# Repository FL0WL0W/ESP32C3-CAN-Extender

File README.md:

# ESP32C3 CAN Extender

This module uses an ESP32C3 with WiFi and BLE. 
It has 3 configurable outputs (5V push pull, Open Drain, 12V pullup), 4 analog or digital inputs, CAN transceiver, 
and an automotive power supply so it can be installed directly into a vehicle. It can be programmed and debugged using the edge connector that connects to any standard 
USBC cable. If you decide to order a PCB yourself, make sure to order it as 0.6mm thickness so that the PCB will fit in the USBC connector.
<br/><br/>
The purpose of this module will be to add cruise control, AC control, tachometer output, speedometer output, and fuel consumption output to my LS3 swapped BMW E30.
The LS3 is currently controlled by the stock GM E38 PCM. This PCM (Powertrain Control Module) uses the CAN bus for the aforementioned items, and this is meant to be a bridge from CAN, to 
discrete signals. This job is originally handled by the BCM (Body Control Module), However the BCM includes alot of items that are not needed for a typical swap, and there 
is not very good documentation on the various BCMs available in cars (compatibility, pinout, etc.). In the future, this car will run on an 
<a href="https://github.com/FL0WL0W/EFIGenie">EFIGenie</a> PCM once the software is more mature. This module will then be useful as a CAN extension module.
<br/><br/>
A demo program will be added soon that has all of the aforementioned features hardcoded, but the eventual goal is to utilize the work from my other repositories 
to create a configurable module that can be programmed through a web UI for various tasks. Another potential feature would be to implement an emulation of the ubiquitous ELM327 bluetooth module that can be used to connect to a phone or tablet to read diagnostic codes, read sensors, or create a digital dash.
<br/><br/>
A 3d model of the enclosure will be uploaded soon as well. The plan is to epoxy pot the pcb inside the enclosure to make it waterproof.

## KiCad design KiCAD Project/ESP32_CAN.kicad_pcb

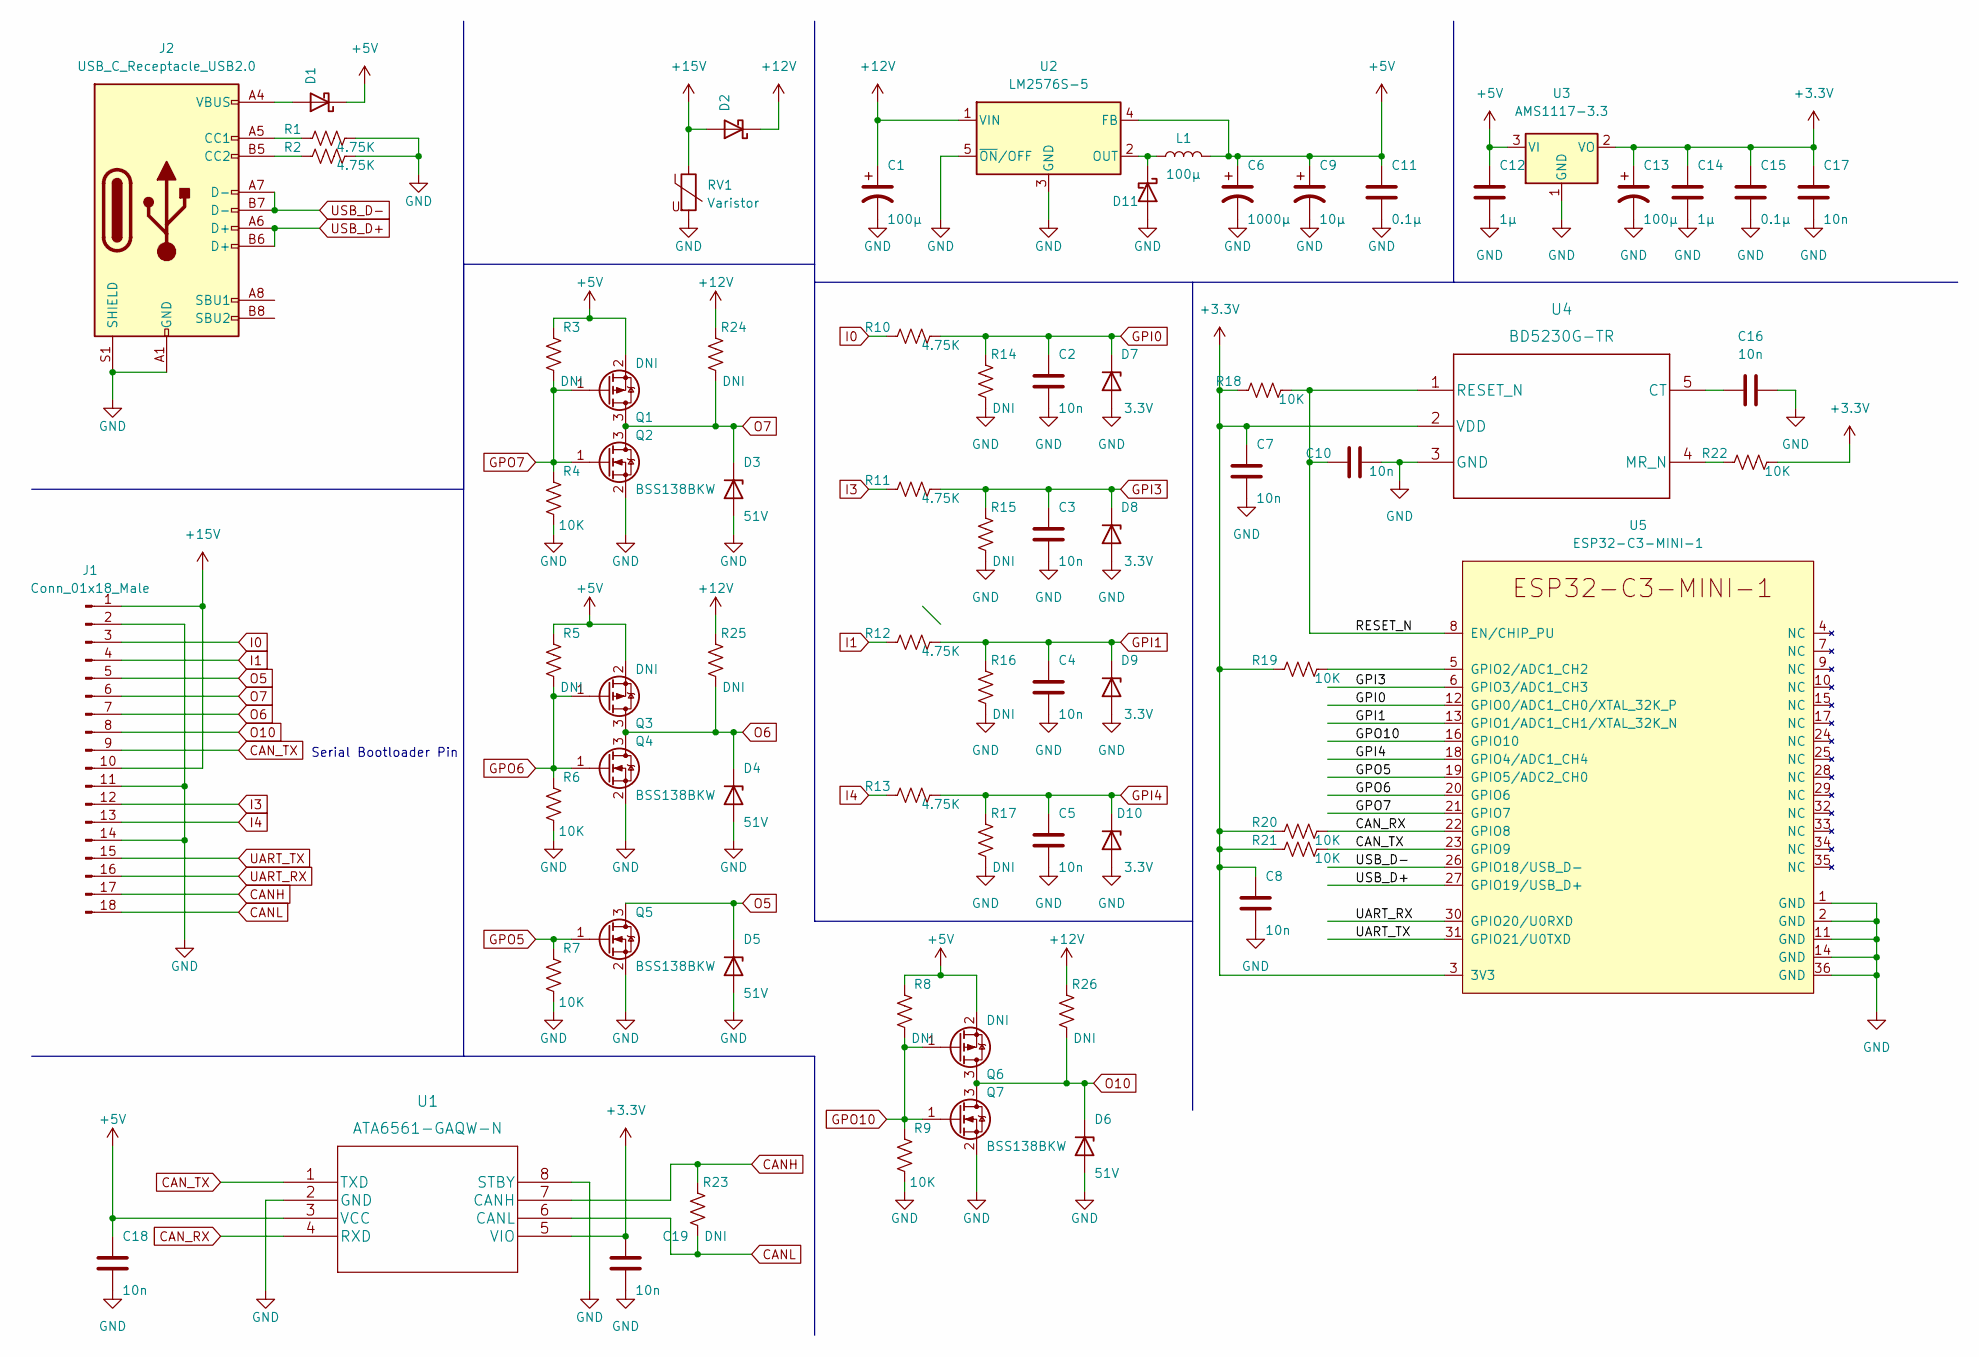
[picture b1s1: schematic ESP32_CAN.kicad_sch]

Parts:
C1, C13: 100μ; CP_Elec_10x10.5
C2, C3, C4, C5, C7, C8, C10, C16, C17, C18, C19: 10n; C_0603_1608Metric_Pad1.08x0.95mm_HandSolder
C6: 1000μ; CP_Elec_10x10.5
C9: 10μ; C_0603_1608Metric_Pad1.08x0.95mm_HandSolder
C11, C15: 0.1μ; C_0603_1608Metric_Pad1.08x0.95mm_HandSolder
C12, C14: 1μ; C_0603_1608Metric_Pad1.08x0.95mm_HandSolder
D1, D2, D11: D_Schottky; D_SOD-123
D3, D4, D5, D6: 51V; D_SOD-123
D7, D8, D9, D10: 3.3V; D_SOD-123
J1: Conn_01x18_Male; MX23A18NF1
J2: USB_C_Receptacle_USB2.0; USB_TYPE_C_DS_5
L1: 100μ; L_12x12mm_H4.5mm
Q1, Q3, Q6: DNI; SOT-323_SC-70_Handsoldering
Q2, Q4, Q5, Q7: BSS138BKW; SOT-323_SC-70_Handsoldering
R1, R2, R10, R11, R12, R13: 4.75K; R_0603_1608Metric_Pad0.98x0.95mm_HandSolder
R3, R5, R8, R14, R15, R16, R17, R23, R24, R25, R26: DNI; R_0603_1608Metric_Pad0.98x0.95mm_HandSolder
R4, R6, R7, R9, R18, R19, R20, R21, R22: 10K; R_0603_1608Metric_Pad0.98x0.95mm_HandSolder
RV1: Varistor; RV_Disc_D15.5mm_W3.9mm_P7.5mm
U1: ATA6561-GAQW-N
U2: LM2576S-5; TO-263-5_TabPin3
U3: AMS1117-3.3; SOT-223-3_TabPin2
U4: BD5230G-TR; TPS3840DL18DBVR
U5: ESP32-C3-MINI-1

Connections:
+3V3: C7.1, C8.1, C13.1, C14.1, C15.1, C17.1, C19.1, R18.1, R19.1, R20.1, R21.1, R22.2, U1.5 (VIO), U3.2 (VO), U4.2 (VDD), U5.3 (3V3)
+5V: C6.1, C9.1, C11.1, C12.1, C18.1, D1.1 (K), L1.2, Q1.2 (S), Q3.2 (S), Q6.2 (S), R3.2, R5.2, R8.2, U1.3 (VCC), U2.4 (FB), U3.3 (VI)
+12V: C1.1, D2.1 (K), R24.2, R25.2, R26.2, U2.1 (VIN)
+15V: D2.2 (A), J1.1, J1.10, RV1.1
/RESET_N: C10.1, R18.2, U4.1 (RESET_N), U5.8 (EN/CHIP_PU)
CANH: J1.17, R23.2, U1.7 (CANH)
CANL: J1.18, R23.1, U1.6 (CANL)
CAN_RX: R20.2, U1.4 (RXD), U5.22 (GPIO8)
CAN_TX: J1.9, R21.2, U1.1 (TXD), U5.23 (GPIO9)
GND: C1.2, C2.2, C3.2, C4.2, C5.2, C6.2, C7.2, C8.2, C9.2, C10.2, C11.2, C12.2, C13.2, C14.2, C15.2, C16.2, C17.2, C18.2, C19.2, D3.2 (A), D4.2 (A), D5.2 (A), D6.2 (A), D7.2 (A), D8.2 (A), D9.2 (A), D10.2 (A), D11.2 (A), J1.2, J1.11, J1.14, J2.A1 (GND), J2.A12 (GND), J2.B1 (GND), J2.B12 (GND), J2.S1 (SHIELD), Q2.2 (S), Q4.2 (S), Q5.2 (S), Q7.2 (S), R1.2, R2.2, R4.1, R6.1, R7.1, R9.1, R14.1, R15.1, R16.1, R17.1, RV1.2, U1.2 (GND), U1.8 (STBY), U2.3 (GND), U2.5 (~ON/OFF), U3.1 (GND), U4.3 (GND), U5.1 (GND), U5.2 (GND), U5.11 (GND), U5.14 (GND), U5.36 (GND)
GPI0: C2.1, D7.1 (K), R10.2, R14.2, U5.12 (GPIO0/ADC1_CH0/XTAL_32K_P)
GPI1: C4.1, D9.1 (K), R12.2, R16.2, U5.13 (GPIO1/ADC1_CH1/XTAL_32K_N)
GPI3: C3.1, D8.1 (K), R11.2, R15.2, U5.6 (GPIO3/ADC1_CH3)
GPI4: C5.1, D10.1 (K), R13.2, R17.2, U5.18 (GPIO4/ADC1_CH4)
GPO5: Q5.1 (G), R7.2, U5.19 (GPIO5/ADC2_CH0)
GPO6: Q3.1 (G), Q4.1 (G), R5.1, R6.2, U5.20 (GPIO6)
GPO7: Q1.1 (G), Q2.1 (G), R3.1, R4.2, U5.21 (GPIO7)
GPO10: Q6.1 (G), Q7.1 (G), R8.1, R9.2, U5.16 (GPIO10)
I0: J1.3, R10.1
I1: J1.4, R12.1
I3: J1.12, R11.1
I4: J1.13, R13.1
unnamed: C16.1, U4.5 (CT)
unnamed: D1.2 (A), J2.A4 (VBUS), J2.A9 (VBUS), J2.B4 (VBUS), J2.B9 (VBUS)
unnamed: D11.1 (K), L1.1, U2.2 (OUT)
unnamed: J2.A5 (CC1), R1.1
unnamed: J2.B5 (CC2), R2.1
unnamed: R19.2, U5.5 (GPIO2/ADC1_CH2)
unnamed: R22.1, U4.4 (MR_N)
O5: D5.1 (K), J1.5, Q5.3 (D)
O6: D4.1 (K), J1.7, Q3.3 (D), Q4.3 (D), R25.1
O7: D3.1 (K), J1.6, Q1.3 (D), Q2.3 (D), R24.1
O10: D6.1 (K), J1.8, Q6.3 (D), Q7.3 (D), R26.1
UART_RX: J1.16, U5.30 (GPIO20/U0RXD)
UART_TX: J1.15, U5.31 (GPIO21/U0TXD)
USB_D+: J2.A6 (D+), J2.B6 (D+), U5.27 (GPIO19/USB_D+)
USB_D-: J2.A7 (D-), J2.B7 (D-), U5.26 (GPIO18/USB_D-)

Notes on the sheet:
Serial Bootloader Pin

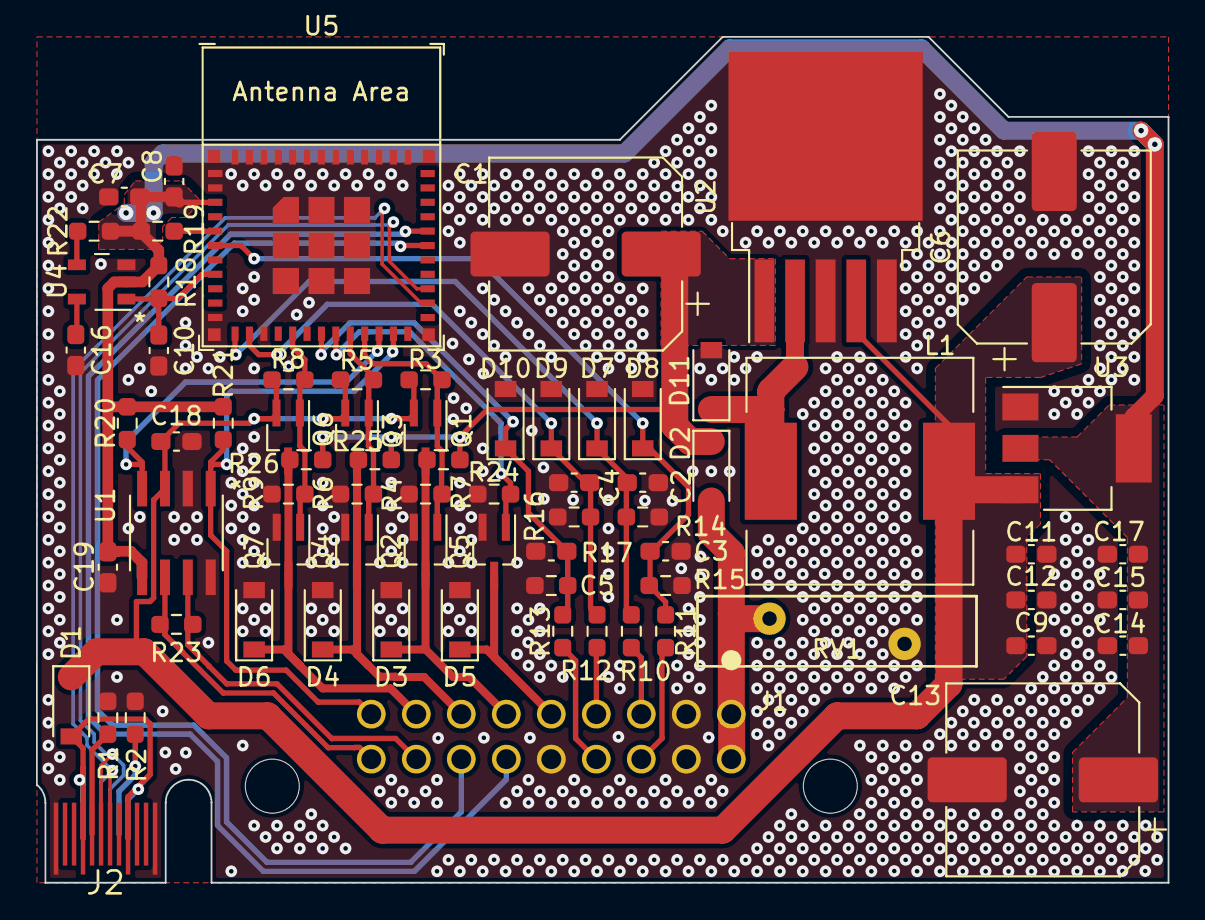
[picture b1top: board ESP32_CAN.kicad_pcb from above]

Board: 2 copper layers, 62.9 x 47.0 mm, 72 parts (0 on the bottom side), 37 nets.

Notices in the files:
parts and their libraries:
Copyright 2021 Accelerated Designs. All rights reserved.
